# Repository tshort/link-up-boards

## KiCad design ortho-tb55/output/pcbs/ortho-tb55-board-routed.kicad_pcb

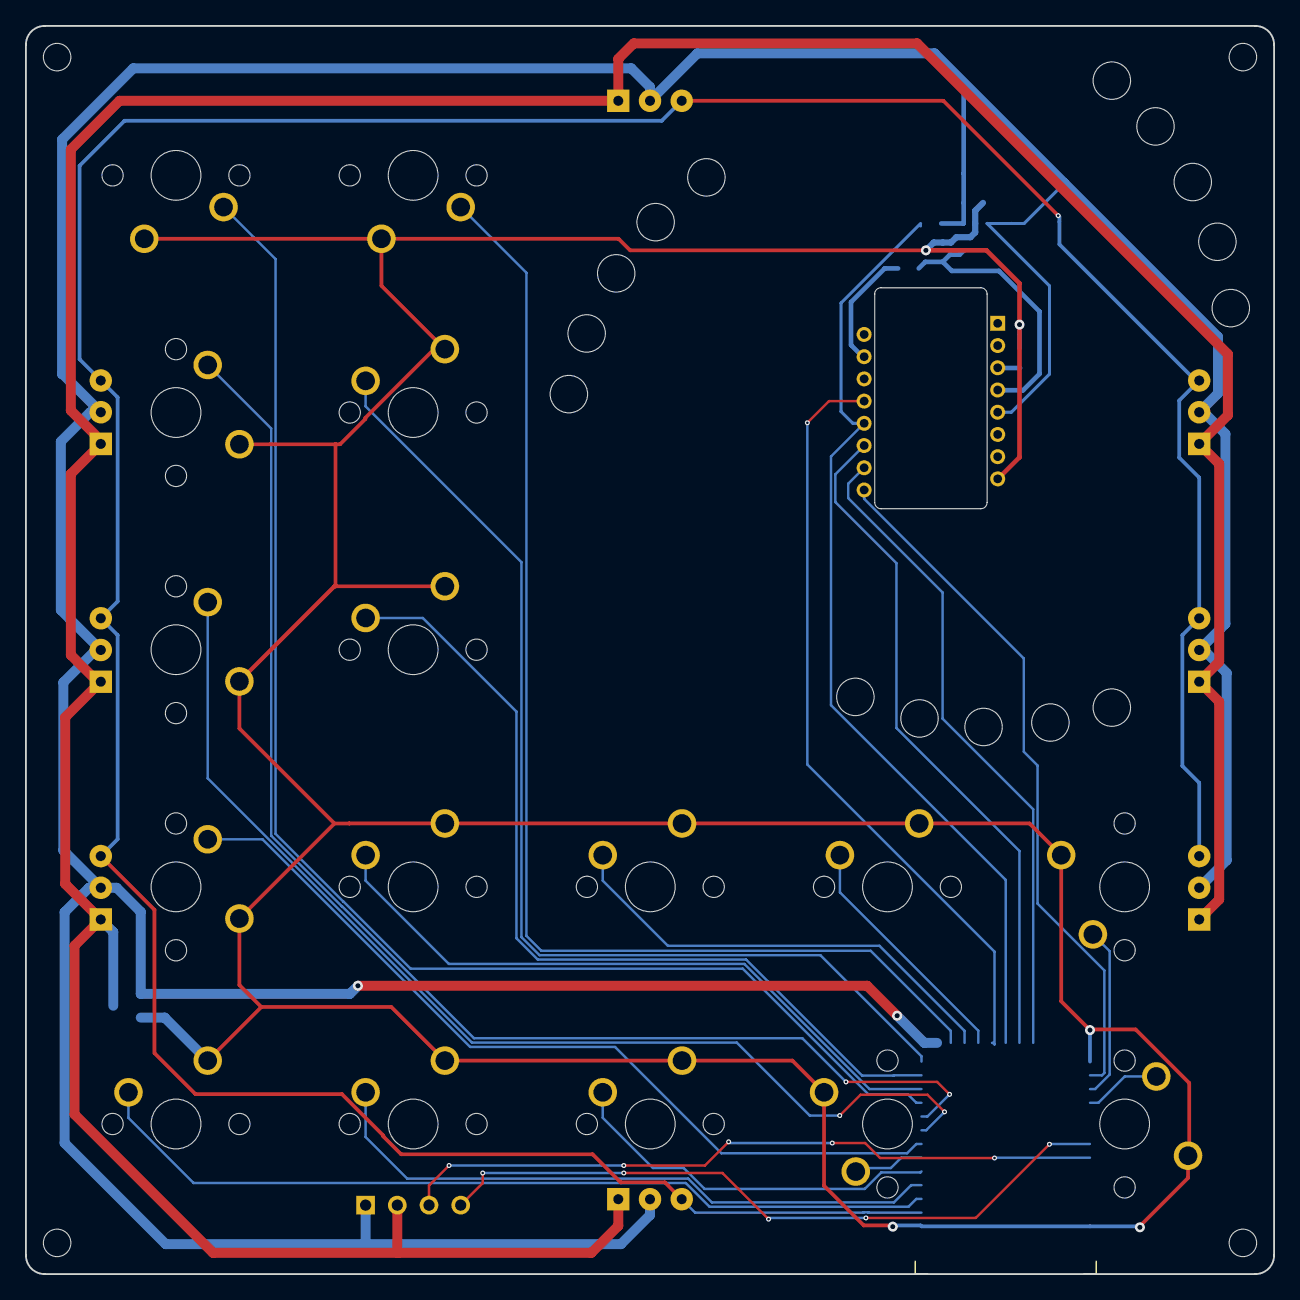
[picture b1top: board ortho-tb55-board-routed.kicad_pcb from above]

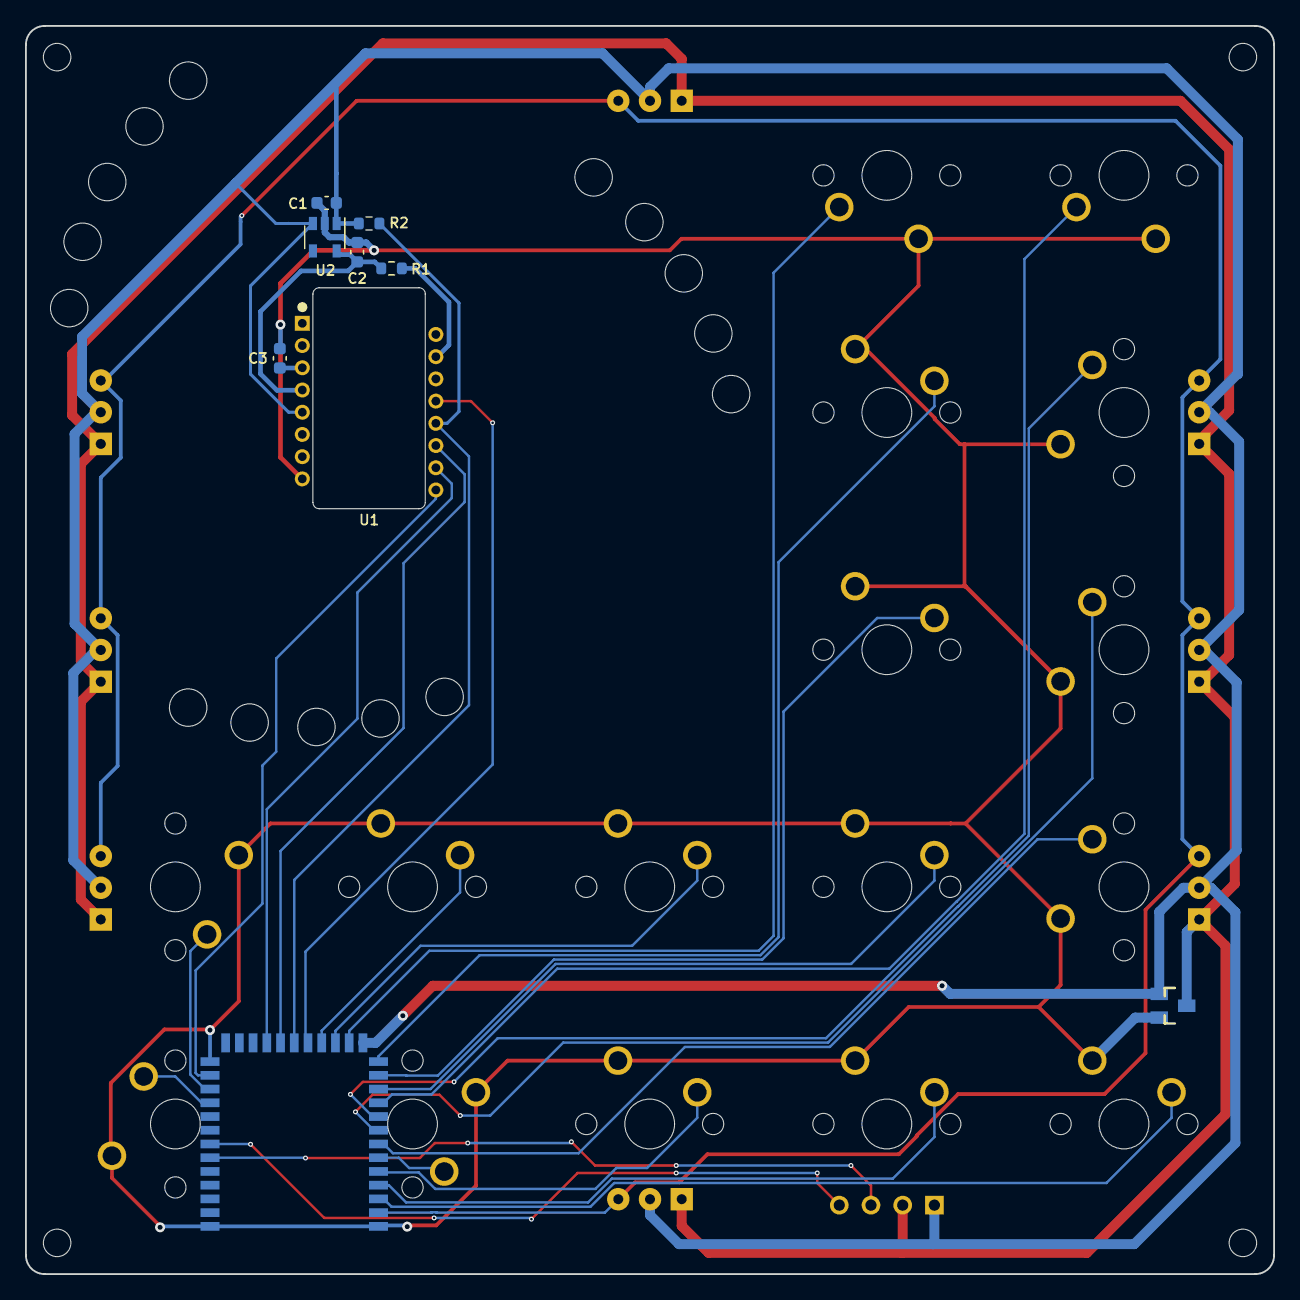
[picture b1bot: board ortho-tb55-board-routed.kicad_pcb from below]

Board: 2 copper layers, 100.0 x 100.0 mm, 23 parts (7 on the bottom side), 3 nets.

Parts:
C1: 0.1u; C_0603_1608Metric
C2: 1u; C_0603_1608Metric
C3: 4.7u; C_0603_1608Metric
R1: 39; R_0603_1608Metric
R2: 10k; R_0603_1608Metric
S1, S2, S3, S4, S5, S6, S7, S8, S9, S10, S11, S12, S13, S14, S15, S16: MX
U1: PMW3360
U2: TCR2EF19; SOT-23-5

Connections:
GND: C1.1, C2.2, C3.2, S1.1, S2.1, S3.1, S4.1, S5.1, S6.1, S7.1, S8.1, S9.1, S10.1, S11.1, S12.1, S13.1, S14.1, S15.1, S16.1, U1.8, U2.2
MISO: R2.2, U1.12
VCC: C1.2, R2.1, U1.5, U2.1, U2.3
